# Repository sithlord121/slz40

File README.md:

# slz40
PCB and keymap files for the SLZ40, a 40s style keyboard with numbers for Zhuyin input.

The PCB requires a Pro Micro (or comparable) controller as well as 58 diodes, 58 MX style switches

The sandwich case takes M2 screws and standoffs.

You can find the key caps required in the following layout.

cap size | number | R1 | R2 | R3 | R4 | R5
-------|-------|-------|-------|------|------|-------|
1u | 47 | 11 | 13 | 10 | 10 | 3 |
1.25u | 6 | 0 | 0 | 1 | 1 | 4 |
1.5u | 1 | 0 | 0 | 0 | 0 | 1 |
1.75u | 4 | 0 | 0 | 1 | 1 | 2 |

[QMK toolbox](https://docs.qmk.fm/#/) is required to flash the layout 

The default keymap can be found in the keymap folder.

A hex of the default layout can be found [here](slz40_default.hex) to make sure the keyboard is working.

--
Update 6/24/2024
Added firmware for Via/Vial compatability.

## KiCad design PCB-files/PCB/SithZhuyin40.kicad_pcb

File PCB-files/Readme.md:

Files needed to print the PCB and sandwich case can be found here

2/7/2023:
Added choc version files.
Firmware is the same.

2/18/2023:
Verified choc version uses the same version of the firmware.

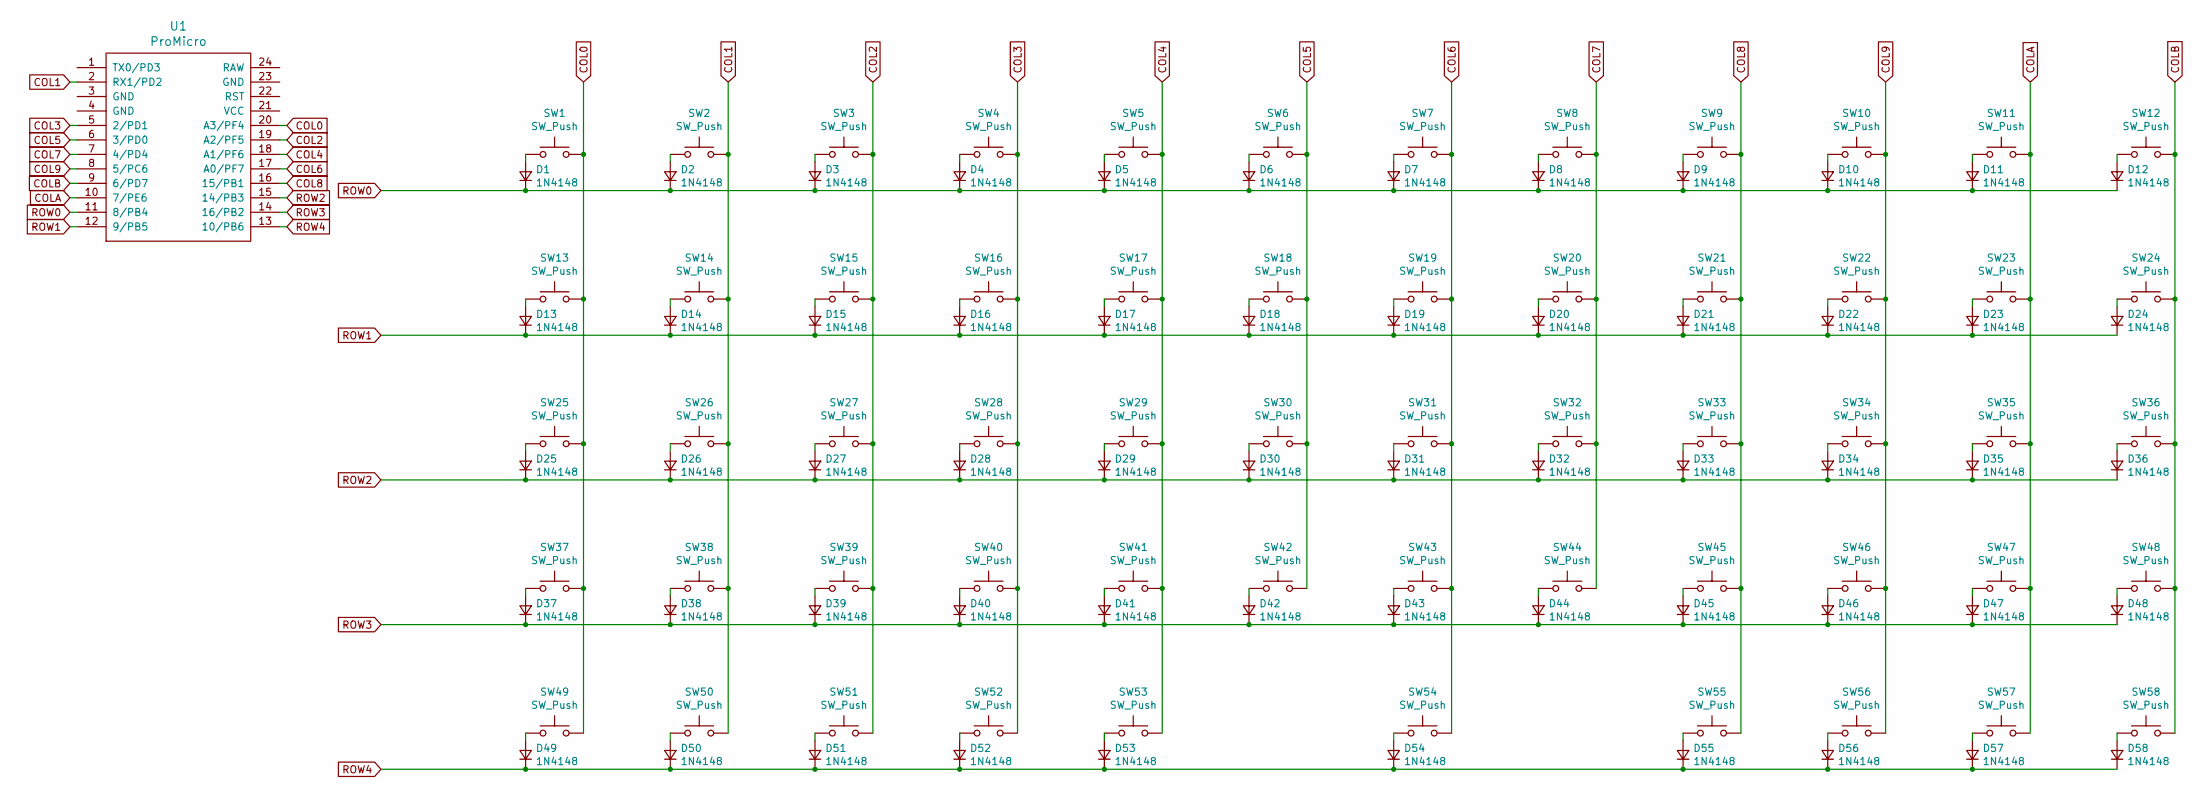
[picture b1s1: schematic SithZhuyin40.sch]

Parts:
D1, D2, D3, D4, D5, D6, D7, D8, D9, D10, D11, D12, D13, D14, D15, D16, D17, D18, D19, D20, D21, D22, D23, D24, D25, D26, D27, D28, D29, D30, D31, D32, D33, D34, D35, D36, D37, D38, D39, D40, D41, D42, D43, D44, D45, D46, D47, D48, D49, D50, D51, D52, D53, D54, D55, D56, D57, D58: 1N4148; Diode-Hybrid-Back
SW1, SW2, SW3, SW4, SW5, SW6, SW7, SW8, SW9, SW10, SW11, SW12, SW13, SW14, SW15, SW16, SW17, SW18, SW19, SW20, SW21, SW22, SW23, SW24, SW26, SW27, SW28, SW29, SW30, SW31, SW32, SW33, SW34, SW35, SW38, SW39, SW40, SW41, SW42, SW43, SW44, SW45, SW46, SW47, SW56, SW57, SW58: SW_Push; MXOnly-1U-NoLED
SW25, SW48, SW49, SW50, SW51, SW52: SW_Push; MXOnly-1.25U-NoLED
SW36, SW37, SW53, SW54: SW_Push; MXOnly-1.75U-NoLED
SW55: SW_Push; MXOnly-1.5U-NoLED
U1: ProMicro; ArduinoProMicro-BackSide

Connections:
COL0: SW1.2, SW13.2, SW25.2, SW37.2, SW49.2, U1.20 (A3/PF4)
COL1: SW2.2, SW14.2, SW26.2, SW38.2, SW50.2, U1.2 (RX1/PD2)
COL2: SW3.2, SW15.2, SW27.2, SW39.2, SW51.2, U1.19 (A2/PF5)
COL3: SW4.2, SW16.2, SW28.2, SW40.2, SW52.2, U1.5 (2/PD1)
COL4: SW5.2, SW17.2, SW29.2, SW41.2, SW53.2, U1.18 (A1/PF6)
COL5: SW6.2, SW18.2, SW30.2, SW42.2, U1.6 (3/PD0)
COL6: SW7.2, SW19.2, SW31.2, SW43.2, SW54.2, U1.17 (A0/PF7)
COL7: SW8.2, SW20.2, SW32.2, SW44.2, U1.7 (4/PD4)
COL8: SW9.2, SW21.2, SW33.2, SW45.2, SW55.2, U1.16 (15/PB1)
COL9: SW10.2, SW22.2, SW34.2, SW46.2, SW56.2, U1.8 (5/PC6)
COLA: SW11.2, SW23.2, SW35.2, SW47.2, SW57.2, U1.10 (7/PE6)
COLB: SW12.2, SW24.2, SW36.2, SW48.2, SW58.2, U1.9 (6/PD7)
unnamed: D1.2 (A), SW1.1
unnamed: D2.2 (A), SW2.1
unnamed: D3.2 (A), SW3.1
unnamed: D4.2 (A), SW4.1
unnamed: D5.2 (A), SW5.1
unnamed: D6.2 (A), SW6.1
unnamed: D7.2 (A), SW7.1
unnamed: D8.2 (A), SW8.1
unnamed: D9.2 (A), SW9.1
unnamed: D10.2 (A), SW10.1
unnamed: D11.2 (A), SW11.1
unnamed: D12.2 (A), SW12.1
unnamed: D13.2 (A), SW13.1
unnamed: D14.2 (A), SW14.1
unnamed: D15.2 (A), SW15.1
unnamed: D16.2 (A), SW16.1
unnamed: D17.2 (A), SW17.1
unnamed: D18.2 (A), SW18.1
unnamed: D19.2 (A), SW19.1
unnamed: D20.2 (A), SW20.1
unnamed: D21.2 (A), SW21.1
unnamed: D22.2 (A), SW22.1
unnamed: D23.2 (A), SW23.1
unnamed: D24.2 (A), SW24.1
unnamed: D25.2 (A), SW25.1
unnamed: D26.2 (A), SW26.1
unnamed: D27.2 (A), SW27.1
unnamed: D28.2 (A), SW28.1
unnamed: D29.2 (A), SW29.1
unnamed: D30.2 (A), SW30.1
unnamed: D31.2 (A), SW31.1
unnamed: D32.2 (A), SW32.1
unnamed: D33.2 (A), SW33.1
unnamed: D34.2 (A), SW34.1
unnamed: D35.2 (A), SW35.1
unnamed: D36.2 (A), SW36.1
unnamed: D37.2 (A), SW37.1
unnamed: D38.2 (A), SW38.1
unnamed: D39.2 (A), SW39.1
unnamed: D40.2 (A), SW40.1
unnamed: D41.2 (A), SW41.1
unnamed: D42.2 (A), SW42.1
unnamed: D43.2 (A), SW43.1
unnamed: D44.2 (A), SW44.1
unnamed: D45.2 (A), SW45.1
unnamed: D46.2 (A), SW46.1
unnamed: D47.2 (A), SW47.1
unnamed: D48.2 (A), SW48.1
unnamed: D49.2 (A), SW49.1
unnamed: D50.2 (A), SW50.1
unnamed: D51.2 (A), SW51.1
unnamed: D52.2 (A), SW52.1
unnamed: D53.2 (A), SW53.1
unnamed: D54.2 (A), SW54.1
unnamed: D55.2 (A), SW55.1
unnamed: D56.2 (A), SW56.1
unnamed: D57.2 (A), SW57.1
unnamed: D58.2 (A), SW58.1
ROW0: D1.1 (K), D2.1 (K), D3.1 (K), D4.1 (K), D5.1 (K), D6.1 (K), D7.1 (K), D8.1 (K), D9.1 (K), D10.1 (K), D11.1 (K), D12.1 (K), U1.11 (8/PB4)
ROW1: D13.1 (K), D14.1 (K), D15.1 (K), D16.1 (K), D17.1 (K), D18.1 (K), D19.1 (K), D20.1 (K), D21.1 (K), D22.1 (K), D23.1 (K), D24.1 (K), U1.12 (9/PB5)
ROW2: D25.1 (K), D26.1 (K), D27.1 (K), D28.1 (K), D29.1 (K), D30.1 (K), D31.1 (K), D32.1 (K), D33.1 (K), D34.1 (K), D35.1 (K), D36.1 (K), U1.15 (14/PB3)
ROW3: D37.1 (K), D38.1 (K), D39.1 (K), D40.1 (K), D41.1 (K), D42.1 (K), D43.1 (K), D44.1 (K), D45.1 (K), D46.1 (K), D47.1 (K), D48.1 (K), U1.14 (16/PB2)
ROW4: D49.1 (K), D50.1 (K), D51.1 (K), D52.1 (K), D53.1 (K), D54.1 (K), D55.1 (K), D56.1 (K), D57.1 (K), D58.1 (K), U1.13 (10/PB6)

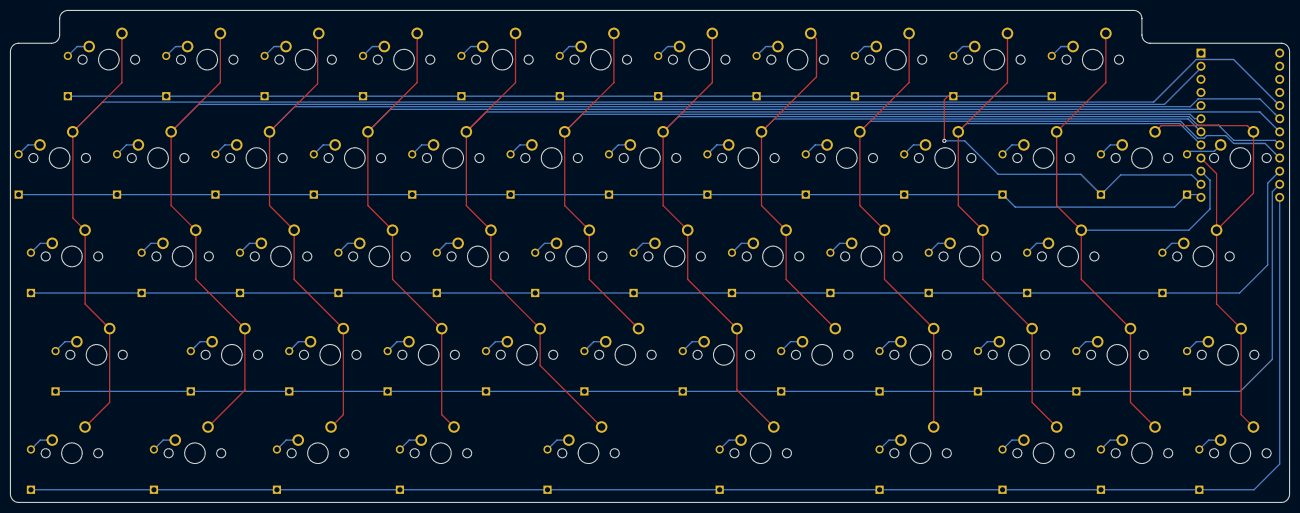
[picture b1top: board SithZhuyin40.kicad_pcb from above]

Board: 2 copper layers, 247.7 x 95.3 mm, 117 parts (0 on the bottom side), 75 nets.

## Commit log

2020-09-12 Create Readme
    to create the folder
2020-09-13 Add files via upload
    PCB files. No silkscreen.
2020-09-13 Update readme.md
    Updated instructions
2020-09-13 Add files via upload
    updated default layout
2020-09-13 added layout picture
2020-09-13 Update README.md
    Updated readme
2020-09-13 Default hex file uploaded
2020-09-13 Update README.md
    Added the hex file for the default layout to the repository and updated readme to link there.
2020-09-13 Delete Readme
    file not needed.
2020-09-20 Add files via upload
    updated default keymap
2020-09-20 Add files via upload
    updated the hex file for the default layout
2020-09-20 Add files via upload
    Forgot F6 to F10 on the layout image
2023-02-20 Delete Bottom.zip
    zip file includes an old version of the gerber, which may be confusing.
2023-10-21 Create Readme.md
    for redacted
2023-10-21 Add files via upload
    default keymap and json file to create custom layouts
2024-06-24 Add files via upload
    Firmware for VIA/VIAL uploaded.
2024-06-24 Add files via upload
    uploaded firmware for SLZ40-redacted via/vial
